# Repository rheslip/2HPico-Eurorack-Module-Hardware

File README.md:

# 2HPico-Eurorack-Module-Hardware
2HP and 4HP Eurorack modules based on Raspberry Pi RP2350 Pico 2

December 2025 - added Version 1.0 2HPico KiCad design files, BOM, Gerbers for main board and panel board and 3D printable panel.

Jan 28/2025 - added Version 1.0 2HPico DSP PCB design files and FR4 front panel design files and gerbers. 

Feb 16/2026 - JLCPCB assembly files are now verifed. Minor BOM changes to 2HPico DSP as a result of further testing.

April 13/2026 - added 4HPico DSP PCB files. PCB fabbed, tested and working with 1 jumper. 

May 6/2026 - updated 4HPico DSP PCB to V1.1 which corrects missing GND plane connection from middle to bottom of PCB. I have no plans to order these because V 1.0 is fine for me. Changes are minimal so not much risk in ordering V1.1.
Added .stl file for 3D printed panel. No plans to do a PCB panel at this point - I'm happy with the 3D printed panel.

2HPico, 2HPico DSP and 4HPico are complimentary designs intended for different uses:

The 2HPico has 1 or 2 CV inputs and 1 or 2 CV outputs depending on how its jumpered - see notes below. Its dual DAC CV output(s) can also be used for audio generated by the RP2350 processor. 2HPico can be used to process triggers, gates and CV inputs and can generate CV or audio out - its well suited for sequencers, LFOs,  oscillators etc.

2HPico DSP has an audio ADC and DAC to enable signal processing for audio effects like delays, reverbs, chorus etc. 

2HPico and 2HPico DSP use the same front panel and control panel PCBs. 

4HPico is basically the 2HPico DSP with stereo audio in and out and two dedicated CV inputs. Encoder with a 64x32 OLED display instead of pots for setting parameters. This is a single PCB design which requires a 3D printed panel or PCB panel.

See the repository https://github.com/rheslip/2HPico-Sketches for Pico Arduino sketches to run on the 2HPico.

See the repository https://github.com/rheslip/2HPico-DSP-Sketches for Pico Arduino sketches to run on the 2HPico DSP.

See the repository https://github.com/rheslip/4HPico-DSP-Sketches for Pico Arduino sketches to run on the 4HPico DSP.

***General notes on the designs***

Waveshare (and others) make small form factor RP2040 and RP2350 boards which make stuffing one into 2HP possible. The RP2350 has much better performance but for simple things like sequencers, ADSR, LFO etc the RP2040 should work OK. Core 0 runs the main processing loop for the UI and control,
core 1 runs the DSP and sends samples to the I2S driver. The code has an option for monitoring the performance of core 1 with a scope. If enabled you will see a pulse on GPIO 8 that indicates how much time core 1 is spending processing samples. If its high more than 100% of the time you will get audio dropouts - time to overclock or optimize your code some more!

The PT8211 16 bit stereo R2R DAC used on the 2HPico is very inexpensive and has proven so far to be quite accurate and consistent from one chip to another (provided they aren't defective - see caveats below). It has no internal antialiasing filters but it works down to DC so can be used as a CV out as well. U6 is a DC coupled antialiasing filter and it also amplifies the DAC output to +-5V eurorack levels.

The 2HPico DSP uses a PCM1808 24 bit stereo audio ADC and a PCM5102A 24 bit stereo audio DAC. The top panel jack is connected to both channels of the PCM1808 and one of the RP2350 ADCs. There is a "DC Input" jumper on the back of the board which shorts the input blocking cap so the top jack can be used for CV input. It adds an approximately 1.6V offset to the input signal so could cause high level audio inputs to clip. Its is recommended to leave the blocking cap in the circuit for audio processing applications.
As with the 2HPico, if the "DAC" solder jumper is shorted audio is sent to both of the lower front panel jacks. Both the PCM1808 and PCM5102A have internal antialiasing filters. Note that the 2HPico DSP can not generate CV outputs because the PCM5102A DAC must be AC coupled.

2HPico DSP build is pretty much the same as the 2HPico but you will be populating a couple of different parts - see the BOM.

***Panel PCB Build notes***

Solder the .1u cap and the RGB LED. Note pin 1 location is NOT the lead with the 45 cut on it - check the picture in the BOM. Hopefully you bought the right pinout! Note these are 5V parts but I haven't had any issues running them at 3.3v - and they are still way too bright!

Solder the jacks - note that the two bottom ones have the same GND via to save real estate

Solder the button. Glue the button cap on with a dab of superglue.

Solder the pots. You can clip the brackets near the bend to make soldering a bit easier but its not required. Make sure they are lined up vertically and horizontally before you solder the brackets to the pads. A Panavise is handy for this step.

***Main PCB Build Notes***

Solder all the 0603 Rs and Cs first

Solder diodes, R1, U3 regulator, U4 voltage reference and power connector J4. Hook it up to power and check that the 5V, -12V, +12V and -10v reference voltages are OK

Solder in all the chips, the larger caps and the trimpot RV1 (2HPico only).

The Waveshare RP2350 board cannot solder directly to the main PCB because it has components on the bottom side and must stand off a bit. You can solder .1" headers to it and solder the headers to the main PCB or solder .1" header pins in the corners and make the rest of the connections with short wires.

Power up the PCB again and check that the 5V and 3.3V rails are OK.

Solder right angle connectors J1, J2 and J3. The shorter pins solder to the main PCB as shown.

Plug the long end of the right angle connectors into the panel PCB and solder.

Clip the pins on the bottom side of the main PCB so they don't interfere with adjacent modules - a 2HP module is supposed to be only 10.16mm wide.

Solder one of the jumper pads on the bottom to select jack 2 on the panel as either DAC right channel out or a second CV/Gate input. This depends on what the module is supposed to do.

The 2HPico DSP board has a "DC Input" solder jumper that should be shorted if you want to use the top jack as a CV input.

It should be ready to go. You can load up the HWtest sketch and run it to check the pots, button, inputs and DAC functions.

***2HPico only - Trim the DAC output***

Load up the ADSR app or mod the HWtest sketch so the I2S code is sending the value 0 to the DACs. Measure the level at the output jacks or at U6 pins 1 and 14 and trim RV1 to get as close to 0V as possible. There will probably still be a few mV difference between the channels. 
Its set up for +-5V output corresponding to -32767 and 32767 DAC values respectively (output amp inverts the DAC signals). If you want higher output levels you can mod the output stage gain but keep in mind the offset and the lowpass filters also have to be recalculated.

***Notes on the PT8211 DAC chips for the 2HPico*** 

I bought 10 on Aliexpress and I got a couple of defective ones. Symptom was no output from either left or right DAC, just a low amplitude glitch at the opamp outputs U6 pins 1 and 14. I suggest you buy from a couple of different vendors and cross your fingers. Alternatively Sparkfun and PJRC sell PT8211 kits for a few dollars that include a PT8211 presumably from a reputable source.

***Notes on the PCM1808 and PCM5012A chips for the 2HPico DSP*** 

The PCM1808 ADC is 24 bit only wheras the PCM5102A works with either 16 bit or 24 bit I2S audio. Since they are on the same I2S interface they must both run the same format. I was not able to get 24 bit I2S working with Arduino Pico but it does work with 32 bit I2S. The additional overhead is minimal since the processor and DMA are 32 bits.

***Notes on the Panels***

STL file is included for a 3D printable panel which includes a collimator that sits over the RGB LED. I glued a short piece of transparent filament inside the collimator as a light pipe - for some reason commercial acrylic light pipes are stupidly expensive. The RGB LED is very bright even on 3.3v so I cut the level back in the code. I will probably design a silkscreened FR4 panel for it at some point.

FR4 front panel gerbers are also included. You will have to make a collimator from a small piece of plastic tubing to direct the RGB LED light to the hole in the panel.

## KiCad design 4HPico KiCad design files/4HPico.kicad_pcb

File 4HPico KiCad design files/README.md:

# 4HPico-Eurorack-Module-Hardware

4HP Eurorack module based on Raspberry Pi RP2350 Pico 2

April 13/2026 - added 4HPico KiCad files. Untested as of 4/13/2026. Panel design TBD.

4HPico is basically the 2HPico DSP with stereo audio in and out and two dedicated CV inputs. Encoder with a 64x32 OLED display instead of pots for setting parameters. This is a single PCB design which requires a 3D printed panel or PCB panel.

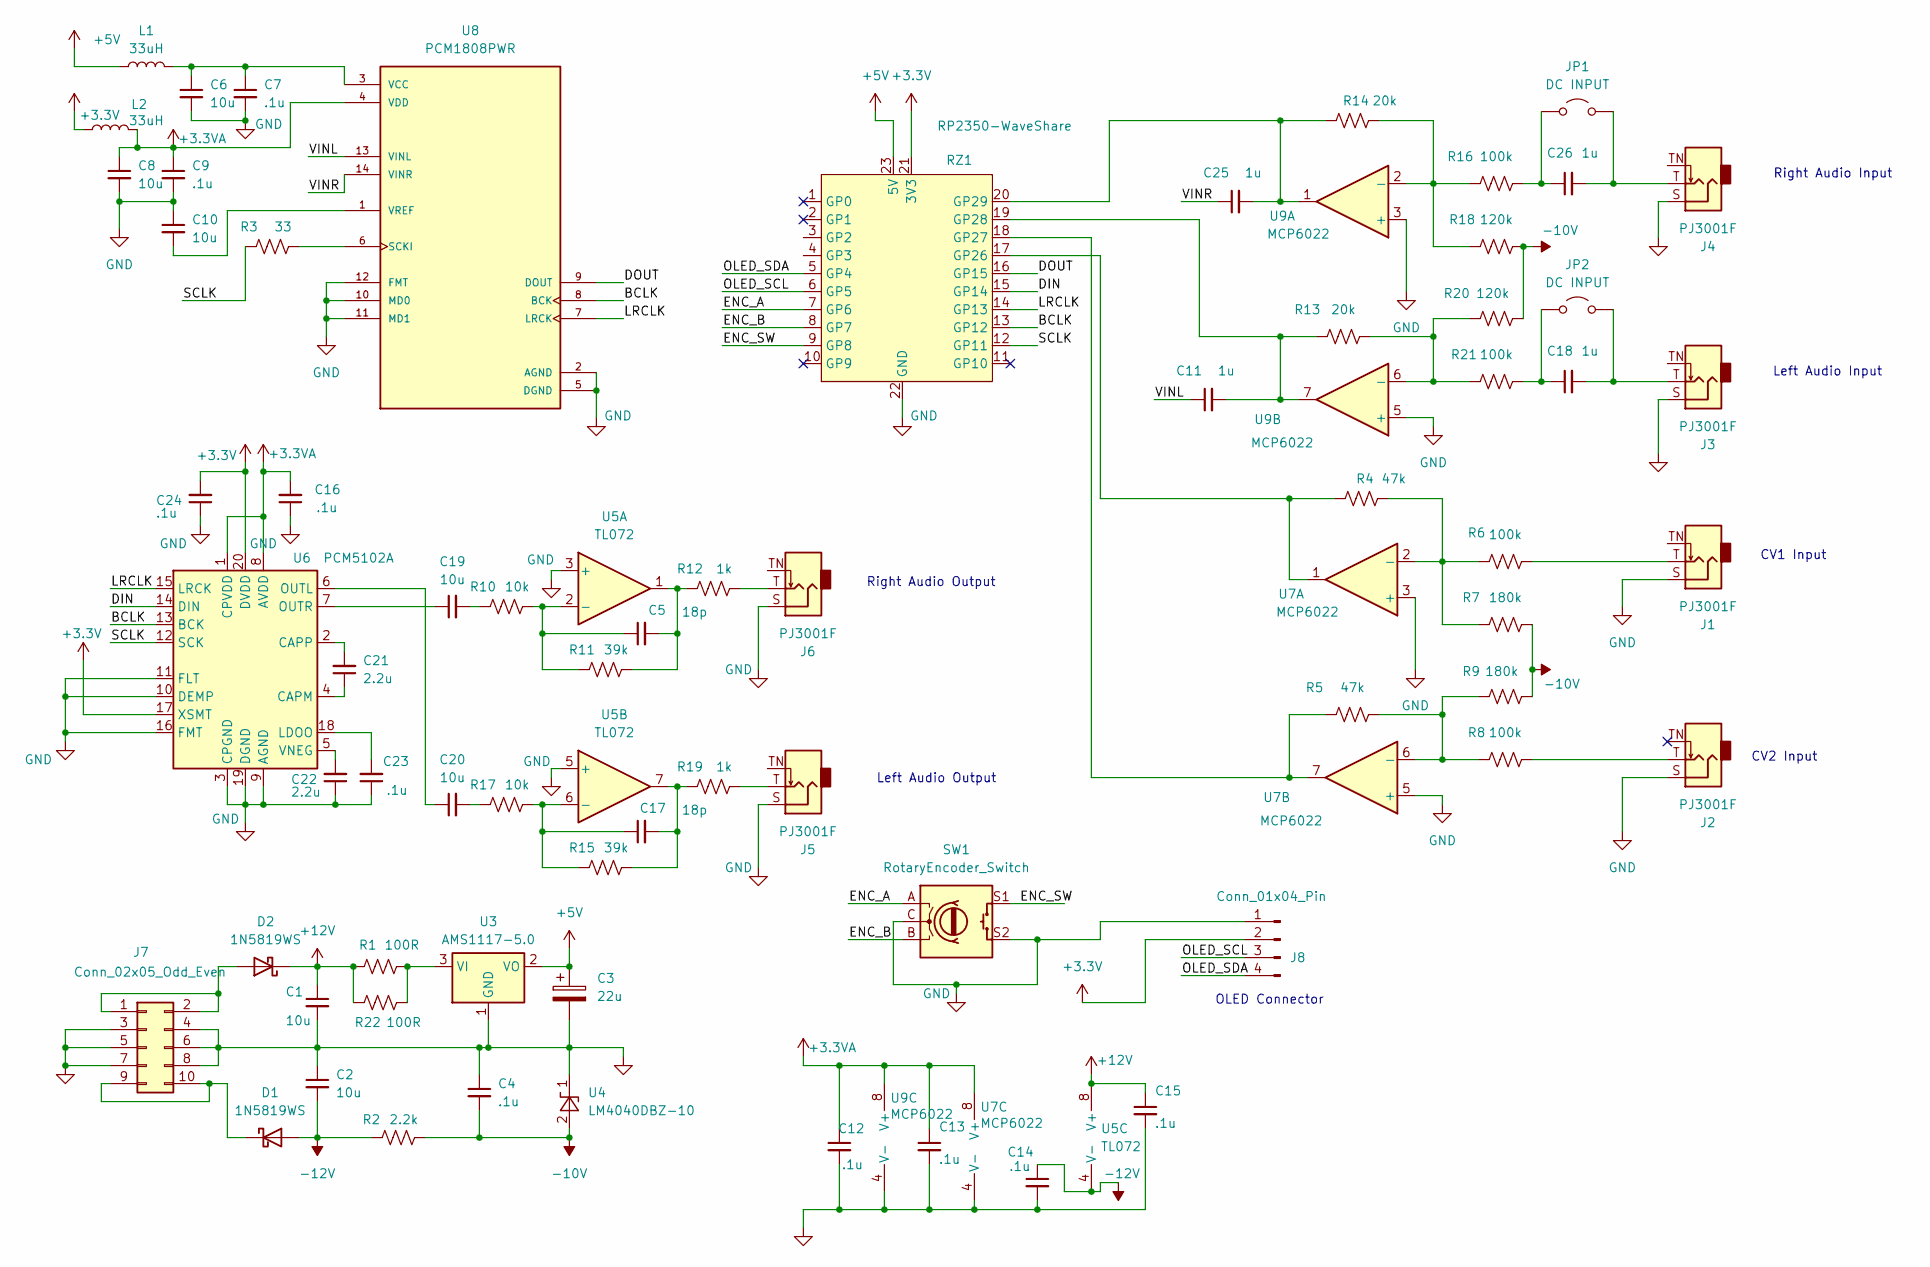
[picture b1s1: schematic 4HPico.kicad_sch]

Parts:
C1, C2, C6, C8, C10, C19, C20: 10u; C_0603_1608Metric_Pad1.08x0.95mm_HandSolder
C3: 22u; CP_Elec_5x5.9
C4, C7, C9, C12, C13, C14, C15, C16, C23, C24: .1u; C_0603_1608Metric_Pad1.08x0.95mm_HandSolder
C5, C17: 18p; C_0603_1608Metric_Pad1.08x0.95mm_HandSolder
C11, C18, C25, C26: 1u; C_0603_1608Metric_Pad1.08x0.95mm_HandSolder
C21, C22: 2.2u; C_0603_1608Metric_Pad1.08x0.95mm_HandSolder
D1, D2: 1N5819WS; D_SOD-123
J1, J2, J3, J4, J5, J6: PJ3001F; AudioJack_3.5mm
J7: Conn_02x05_Odd_Even; PinHeader_2x05_P2.54mm_Vertical
J8: Conn_01x04_Pin; PinHeader_1x04_P2.54mm_Vertical
JP1, JP2: DC INPUT; SolderJumper-2_P1.3mm_Open_RoundedPad1.0x1.5mm
L1, L2: 33uH; L_0603_1608Metric_Pad1.05x0.95mm_HandSolder
R1, R22: 100R; R_1206_3216Metric_Pad1.30x1.75mm_HandSolder
R2: 2.2k; R_0603_1608Metric_Pad0.98x0.95mm_HandSolder
R3: 33; R_0603_1608Metric_Pad0.98x0.95mm_HandSolder
R4, R5: 47k; R_0603_1608Metric_Pad0.98x0.95mm_HandSolder
R6, R8, R16, R21: 100k; R_0603_1608Metric_Pad0.98x0.95mm_HandSolder
R7, R9: 180k; R_0603_1608Metric_Pad0.98x0.95mm_HandSolder
R10, R17: 10k; R_0603_1608Metric_Pad0.98x0.95mm_HandSolder
R11, R15: 39k; R_0603_1608Metric_Pad0.98x0.95mm_HandSolder
R12, R19: 1k; R_0603_1608Metric_Pad0.98x0.95mm_HandSolder
R13, R14: 20k; R_0603_1608Metric_Pad0.98x0.95mm_HandSolder
R18, R20: 120k; R_0603_1608Metric_Pad0.98x0.95mm_HandSolder
RZ1: RP2350-WaveShare; RP2350-Waveshare
SW1: RotaryEncoder_Switch; RotaryEncoder_Alps_EC11E-Switch_Vertical_H20mm_topsolder
U3: AMS1117-5.0; SOT-223-3_TabPin2
U4: LM4040DBZ-10; SOT-23
U5: TL072; SOIC-8_3.9x4.9mm_P1.27mm
U6: PCM5102A; TSSOP-20_4.4x6.5mm_P0.65mm
U7, U9: MCP6022; SOIC-8_3.9x4.9mm_P1.27mm
U8: PCM1808PWR; TSSOP-14_4.4x5mm_P0.65mm; PARTREV B; DigiKey_Part_Number 296-26307-1-ND

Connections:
+3.3V: C24.2, J8.2, L2.1, RZ1.21 (3V3), U6.17 (XSMT), U6.20 (DVDD)
+3.3VA: C8.1, C9.1, C12.1, C13.1, C16.2, L2.2, U6.1 (CPVDD), U6.8 (AVDD), U7.8 (V+), U8.4 (VDD), U9.8 (V+)
+5V: C3.1, L1.1, RZ1.23 (5V), U3.2 (VO)
+12V: C1.1, C15.1, D2.1 (K), R1.1, R22.1, U5.8 (V+)
-10V: C4.2, R2.2, R7.2, R9.2, R18.2, R20.2, U4.2 (A)
-12V: C2.2, C14.1, D1.2 (A), R2.1, U5.4 (V-)
/BCLK: RZ1.13 (GP12), U6.13 (BCK), U8.8 (BCK)
/DIN: RZ1.15 (GP14), U6.14 (DIN)
/DOUT: RZ1.16 (GP15), U8.9 (DOUT)
/ENC_A: RZ1.7 (GP6), SW1.A
/ENC_B: RZ1.8 (GP7), SW1.B
/ENC_SW: RZ1.9 (GP8), SW1.S1
/LRCLK: RZ1.14 (GP13), U6.15 (LRCK), U8.7 (LRCK)
/OLED_SCL: J8.3, RZ1.6 (GP5)
/OLED_SDA: J8.4, RZ1.5 (GP4)
/SCLK: R3.1, RZ1.12 (GP11), U6.12 (SCK)
/VINL: C11.1, U8.13 (VINL)
/VINR: C25.1, U8.14 (VINR)
GND: C1.2, C2.1, C3.2, C4.1, C6.2, C7.2, C8.2, C9.2, C10.1, C12.2, C13.2, C14.2, C15.2, C16.1, C22.1, C23.1, C24.1, J1.S, J2.S, J3.S, J4.S, J5.S, J6.S, J7.3, J7.4, J7.5, J7.6, J7.7, J7.8, J8.1, RZ1.22 (GND), SW1.C, SW1.S2, U3.1 (GND), U4.1 (K), U5.3 (+), U5.5 (+), U6.3 (CPGND), U6.9 (AGND), U6.10 (DEMP), U6.11 (FLT), U6.16 (FMT), U6.19 (DGND), U7.3 (+), U7.4 (V-), U7.5 (+), U8.2 (AGND), U8.5 (DGND), U8.10 (MD0), U8.11 (MD1), U8.12 (FMT), U9.3 (+), U9.4 (V-), U9.5 (+)
unnamed: C5.2, R11.2, R12.1, U5.1
unnamed: C17.2, R15.2, R19.1, U5.7
unnamed: C19.2, R10.1
unnamed: C20.2, R17.1
unnamed: D1.1 (K), J7.9, J7.10
unnamed: D2.2 (A), J7.1, J7.2
unnamed: J1.T, R6.2
unnamed: J2.T, R8.2
unnamed: J5.T, R19.2
unnamed: J6.T, R12.2
unnamed: C26.1, JP1.1 (A), R16.2
unnamed: C26.2, J4.T, JP1.2 (B)
unnamed: C18.1, JP2.1 (A), R21.2
unnamed: C18.2, J3.T, JP2.2 (B)
unnamed: R4.1, RZ1.17 (GP26), U7.1
unnamed: R5.1, RZ1.18 (GP27), U7.7
unnamed: C11.2, R13.1, RZ1.19 (GP28), U9.7
unnamed: C25.2, R14.1, RZ1.20 (GP29), U9.1
unnamed: R1.2, R22.2, U3.3 (VI)
unnamed: C5.1, R10.2, R11.1, U5.2 (-)
unnamed: C17.1, R15.1, R17.2, U5.6 (-)
unnamed: C21.1, U6.4 (CAPM)
unnamed: C21.2, U6.2 (CAPP)
unnamed: C23.2, U6.18 (LDOO)
unnamed: C20.1, U6.6 (OUTL)
unnamed: C19.1, U6.7 (OUTR)
unnamed: C22.2, U6.5 (VNEG)
unnamed: R4.2, R6.1, R7.1, U7.2 (-)
unnamed: R5.2, R8.1, R9.1, U7.6 (-)
unnamed: R3.2, U8.6 (SCKI)
unnamed: C6.1, C7.1, L1.2, U8.3 (VCC)
unnamed: C10.2, U8.1 (VREF)
unnamed: R14.2, R16.1, R18.1, U9.2 (-)
unnamed: R13.2, R20.1, R21.1, U9.6 (-)

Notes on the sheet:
CV2 Input
Left Audio Output
Left Audio Input
CV1 Input
OLED Connector
Right Audio Input
Right Audio Output

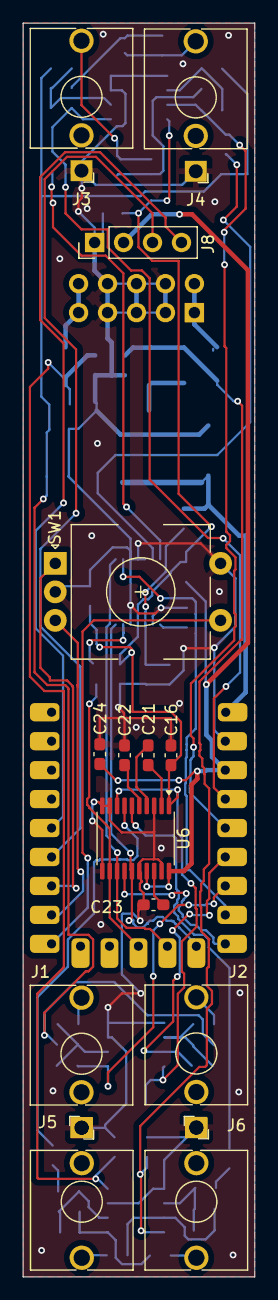
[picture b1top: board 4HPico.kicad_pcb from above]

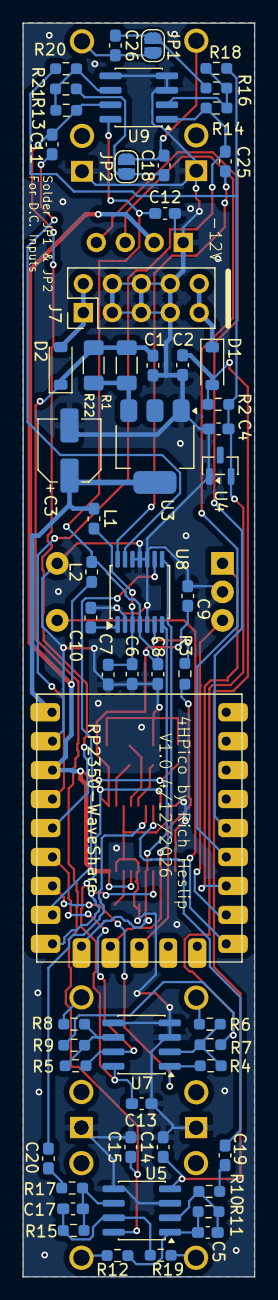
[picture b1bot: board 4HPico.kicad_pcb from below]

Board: 2 copper layers, 20.3 x 110.0 mm, 71 parts (57 on the bottom side), 53 nets.

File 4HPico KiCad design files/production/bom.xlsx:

Designator | Footprint | Quantity | Value | LCSC Part #
C1, C10, C19, C2, C20, C6, C8 | 603 | 7 | 10u
C11, C18, C25, C26 | 603 | 4 | 1u
C12, C13, C14, C15, C16, C23, C24, C4, C7, C9 | 603 | 10 | .1u
C17, C5 | 603 | 2 | 18p
C21, C22 | 603 | 2 | 2.2u
C3 | CP_Elec_5x5.9 | 1 | 22u
D1, D2 | D_SOD-123 | 2 | 1N5819WS
J1, J2, J3, J4, J5, J6 | AudioJack_3.5mm | 6 | PJ3001F
J7 | PinHeader_2x05_P2.54mm_Vertical | 1 | Conn_02x05_Odd_Even
J8 | PinHeader_1x04_P2.54mm_Vertical | 1 | Conn_01x04_Pin
JP1, JP2 | SolderJumper-2_P1.3mm_Open_RoundedPad1.0x1.5mm | 2 | DC INPUT
L1, L2 | 603 | 2 | 33uH
R1, R22 | 1206 | 2 | 100R
R10, R17 | 603 | 2 | 10k
R11, R15 | 603 | 2 | 39k
R12, R19 | 603 | 2 | 1k
R13, R14 | 603 | 2 | 20k
R16, R21, R6, R8 | 603 | 4 | 100k
R18, R20 | 603 | 2 | 120k
R2 | 603 | 1 | 2.2k
R3 | 603 | 1 | 33
R4, R5 | 603 | 2 | 47k
R7, R9 | 603 | 2 | 180k
RZ1 | RP2350-Waveshare | 1 | RP2350-WaveShare
SW1 | RotaryEncoder_Alps_EC11E-Switch_Vertical_H20mm_topsolder | 1 | RotaryEncoder_Switch
U3 | SOT-223-3_TabPin2 | 1 | AMS1117-5.0
U4 | SOT-23 | 1 | LM4040DBZ-10
U5 | SOIC-8_3.9x4.9mm_P1.27mm | 1 | TL072
U6 | TSSOP-20_4.4x6.5mm_P0.65mm | 1 | PCM5102A
U7, U9 | SOIC-8_3.9x4.9mm_P1.27mm | 2 | MCP6022
U8 | TSSOP-14_4.4x5mm_P0.65mm | 1 | PCM1808PWR

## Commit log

2025-12-19 Updated BOMs, added images
    added more details in BOM and pics of boards
2025-12-20 Updated readme
    Added build notes
2025-12-20 updated readme
    updated readme
2026-01-28 Added 2HPico DSP version and FR4 front panel designs
    New 2HPico DSP board (called 2HPico audio in the archive). Added FR4 front panel as an alternative to the 3D printed panel
2026-02-05 Added JLCPCB Assembly files
    Thanks to Blake for the assembly files!
2026-02-16 Updated 2HPico DSP schematic, BOM and JLCPCB assy files
    BOM changes as a result of further testing: R1 -> 47 ohms, R10,R17->10k.
2026-04-13 Added 4HPico design files
    4HPico is an expanded version of the 2HPico DSP.
2026-05-06 Updated to V1.1
    Connected middle and bottom GND planes. Added panel .stl file for 3D printing.
2026-05-07 Updated 4HPico BOM
    4HPico BOM update, added PDF schematic
